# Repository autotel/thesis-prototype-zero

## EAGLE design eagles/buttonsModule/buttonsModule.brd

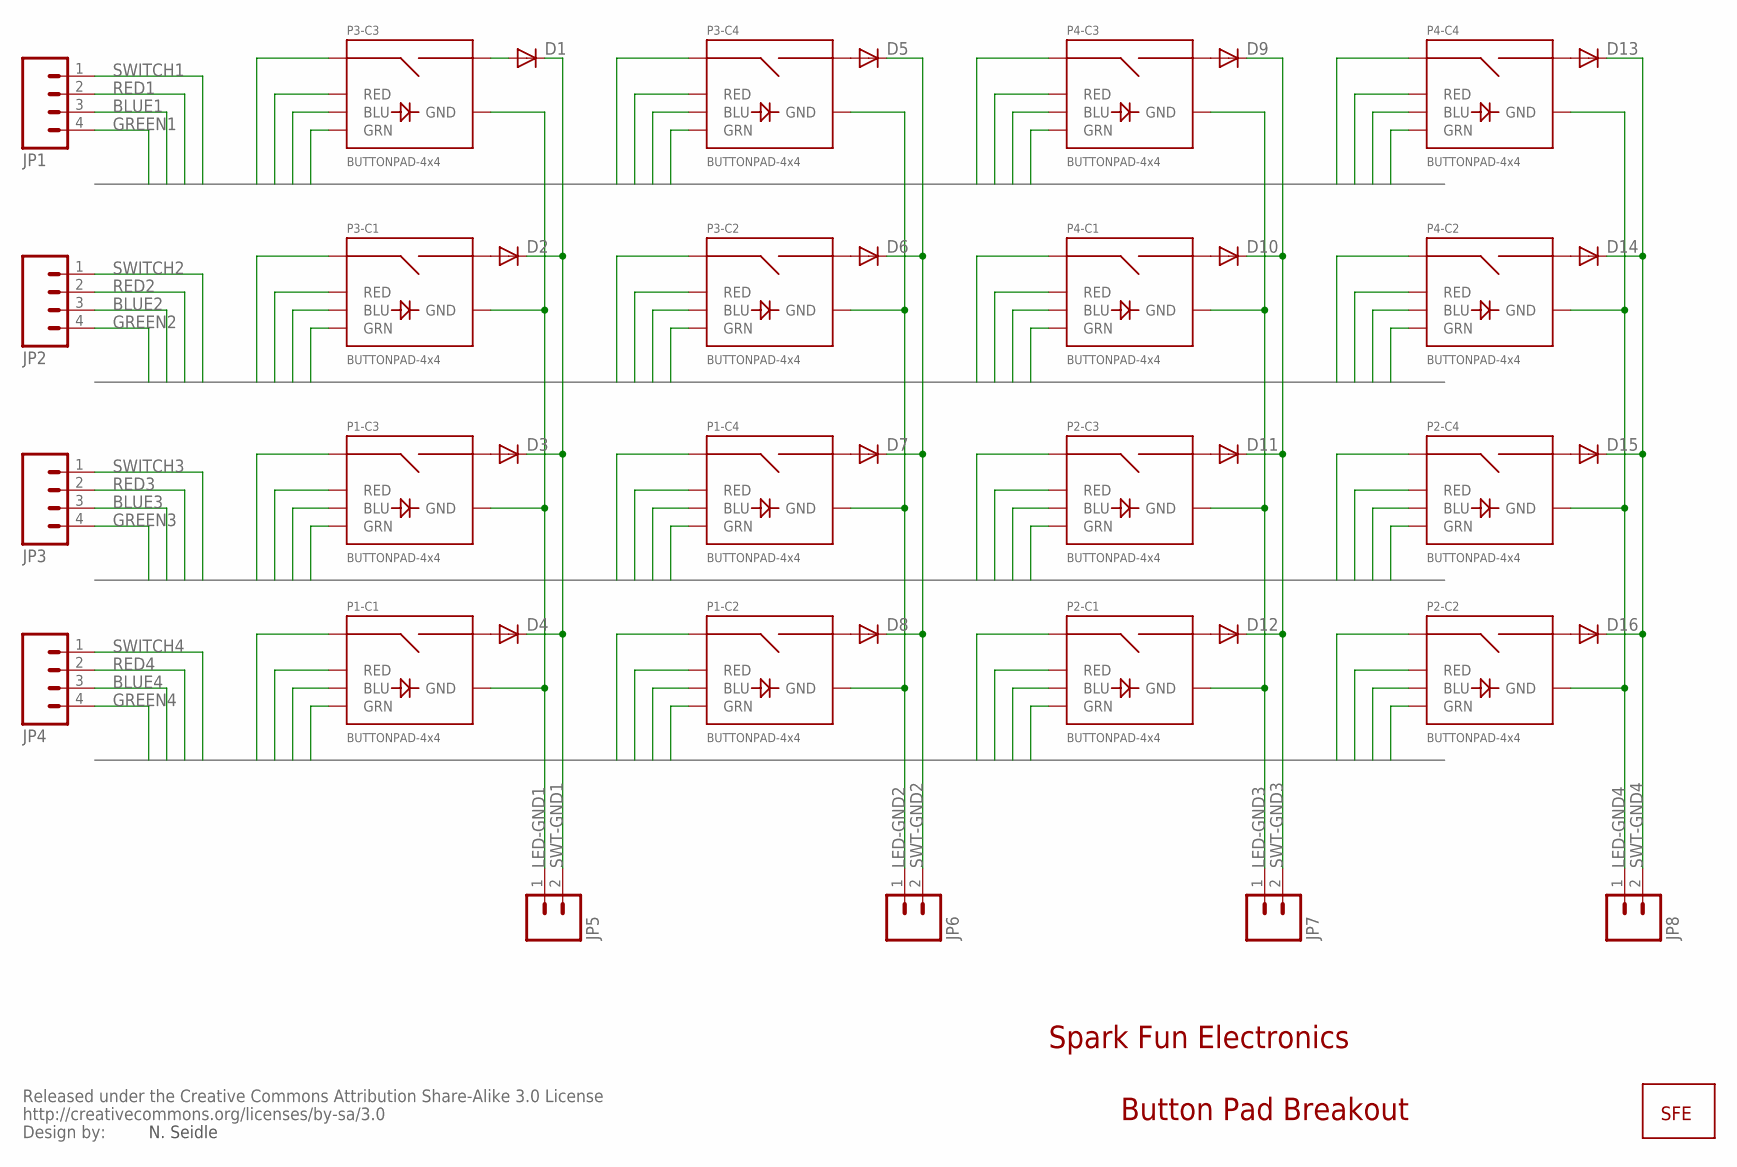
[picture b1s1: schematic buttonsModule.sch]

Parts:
D1, D2, D3, D4, D5, D6, D7, D8, D9, D10, D11, D12, D13, D14, D15, D16: DIODE-1N4148; DOIDE-1N4148
JP1, JP2, JP3, JP4: M04POLAR; MOLEX-1X4
JP5, JP6, JP7, JP8: M02POLAR; MOLEX-1X2
P1, P2, P3, P4: BUTTONPAD-4x4; BUTTONPAD-2X2
U$1: LOGO-SFE; SFE-NEW-WEBLOGO
U$2: CREATIVE_COMMONS

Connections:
BLUE1: JP1.3, P3.BLU3 (BLU), P3.BLU4 (BLU), P4.BLU3 (BLU), P4.BLU4 (BLU)
BLUE2: JP2.3, P3.BLU1 (BLU), P3.BLU2 (BLU), P4.BLU1 (BLU), P4.BLU2 (BLU)
BLUE3: JP3.3, P1.BLU3 (BLU), P1.BLU4 (BLU), P2.BLU3 (BLU), P2.BLU4 (BLU)
BLUE4: JP4.3, P1.BLU1 (BLU), P1.BLU2 (BLU), P2.BLU1 (BLU), P2.BLU2 (BLU)
GREEN1: JP1.4, P3.GRN3 (GRN), P3.GRN4 (GRN), P4.GRN3 (GRN), P4.GRN4 (GRN)
GREEN2: JP2.4, P3.GRN1 (GRN), P3.GRN2 (GRN), P4.GRN1 (GRN), P4.GRN2 (GRN)
GREEN3: JP3.4, P1.GRN3 (GRN), P1.GRN4 (GRN), P2.GRN3 (GRN), P2.GRN4 (GRN)
GREEN4: JP4.4, P1.GRN1 (GRN), P1.GRN2 (GRN), P2.GRN1 (GRN), P2.GRN2 (GRN)
LED-GND1: JP5.1, P1.GND1 (GND), P1.GND3 (GND), P3.GND1 (GND), P3.GND3 (GND)
LED-GND2: JP6.1, P1.GND2 (GND), P1.GND4 (GND), P3.GND2 (GND), P3.GND4 (GND)
LED-GND3: JP7.1, P2.GND1 (GND), P2.GND3 (GND), P4.GND1 (GND), P4.GND3 (GND)
LED-GND4: JP8.1, P2.GND2 (GND), P2.GND4 (GND), P4.GND2 (GND), P4.GND4 (GND)
unnamed: D1.P$1 (A), P3.SIG6 (SIG2)
unnamed: D2.P$1 (A), P3.SIG2
unnamed: D3.P$1 (A), P1.SIG6 (SIG2)
unnamed: D4.P$1 (A), P1.SIG2
unnamed: D5.P$1 (A), P3.SIG8 (SIG2)
unnamed: D6.P$1 (A), P3.SIG4 (SIG2)
unnamed: D7.P$1 (A), P1.SIG8 (SIG2)
unnamed: D8.P$1 (A), P1.SIG4 (SIG2)
unnamed: D9.P$1 (A), P4.SIG6 (SIG2)
unnamed: D10.P$1 (A), P4.SIG2
unnamed: D11.P$1 (A), P2.SIG6 (SIG2)
unnamed: D12.P$1 (A), P2.SIG2
unnamed: D13.P$1 (A), P4.SIG8 (SIG2)
unnamed: D14.P$1 (A), P4.SIG4 (SIG2)
unnamed: D15.P$1 (A), P2.SIG8 (SIG2)
unnamed: D16.P$1 (A), P2.SIG4 (SIG2)
RED1: JP1.2, P3.RED3 (RED), P3.RED4 (RED), P4.RED3 (RED), P4.RED4 (RED)
RED2: JP2.2, P3.RED1 (RED), P3.RED2 (RED), P4.RED1 (RED), P4.RED2 (RED)
RED3: JP3.2, P1.RED3 (RED), P1.RED4 (RED), P2.RED3 (RED), P2.RED4 (RED)
RED4: JP4.2, P1.RED1 (RED), P1.RED2 (RED), P2.RED1 (RED), P2.RED2 (RED)
SWITCH1: JP1.1, P3.SIG5 (SIG1), P3.SIG7 (SIG1), P4.SIG5 (SIG1), P4.SIG7 (SIG1)
SWITCH2: JP2.1, P3.SIG1, P3.SIG3 (SIG1), P4.SIG1, P4.SIG3 (SIG1)
SWITCH3: JP3.1, P1.SIG5 (SIG1), P1.SIG7 (SIG1), P2.SIG5 (SIG1), P2.SIG7 (SIG1)
SWITCH4: JP4.1, P1.SIG1, P1.SIG3 (SIG1), P2.SIG1, P2.SIG3 (SIG1)
SWT-GND1: D1.P$2 (C), D2.P$2 (C), D3.P$2 (C), D4.P$2 (C), JP5.2
SWT-GND2: D5.P$2 (C), D6.P$2 (C), D7.P$2 (C), D8.P$2 (C), JP6.2
SWT-GND3: D9.P$2 (C), D10.P$2 (C), D11.P$2 (C), D12.P$2 (C), JP7.2
SWT-GND4: D13.P$2 (C), D14.P$2 (C), D15.P$2 (C), D16.P$2 (C), JP8.2

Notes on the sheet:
Button Pad Breakout
Spark Fun Electronics
N. Seidle

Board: 2 copper layers, 30 parts (4 on the bottom side), 40 nets, no tracks yet.

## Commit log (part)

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2016-10-20 lcd working, encoder started
2016-10-26 hello button pads no multiplex (monochrome/row)
2016-10-27 leds now count one by one, completing the matrix program
2016-11-03 change led matrix pins to take them out from audio overlap
2016-11-03 idea for replacing lcd pins
2016-11-08 will not work
2016-11-08 mux is also problematic
2016-11-08 handy notes
2016-11-08 perfect led matrix applied to teensy
2016-11-09 undef var remove
2016-11-10 buttons not yet working but implemented
2016-11-14 buttons and led matrix working
2016-11-15 started pcb design
2016-11-16 first time i think that the schematic is ready
2016-11-16 FIX 16*4 pads error
2016-11-17 forward with the pcb design
2016-11-17 board PCB iteration prior to route
2016-11-17 fix big mistake on schematic
2016-11-17 first successful route
2016-11-18 routing job close
2016-11-18 expose contact terminals in button areas by applying solder mask
2016-11-19 successfully adapted the software for screen+button pad matrix using 16x muxes and arduino
2016-11-19 adapt portb connection to fit an LCD breakout
2016-11-19 routed last schematic change in the dip version
2016-11-22 tried to put ledmatrix libraries inside the libraries but couldn't because problems between static and instance modes that i don't understand
2016-11-28 starting to rollback intent to put all functionality in a library+ addition of barrel jack to pcb
2016-11-28 works, not 'libaried' anymore
2017-01-19 button toggle
2017-01-19 onButtonHeld
2017-01-22 midi style memory and interaction
2017-02-13 screeen slightly better, free up pins for screen
2017-02-13 lcd integrated in hardware
2017-02-14 more comments, activated intervace tact switches and duplicated to make a version with ui
2017-02-14 selector buttons now have onpress and onrelease funcs modeselector base
2017-02-14 modeselector is a modifier and not a mode
2017-02-14 cmplete ability to select channels, notes and playing modes using different user interaction schemes
2017-02-14 -split in multiple files - created the interaction for the scale design mode
2017-02-14 prototypes of cc modulation along with notes
2017-02-15 encoder activated notes for improvement of the PCB board
2017-02-16 body for the v2 prorotype started additional notes on the pcb design
2017-02-17 started creating the way for the sequencer, including changes in the ui and memory optimization fixed errors in the enclosure. There are still some to fix
2017-02-18 reduced use of dynamic memory by storing strings in PROGMEM
2017-02-18 basic and buggy implementation of sequencer mode with less memory usage
2017-02-28 checking different screen algorhythms to correct the problems
2017-02-28 changed some hardcoded vars with preprocessor vars
2017-03-02 fixed all known trouble with note matching in sequencer
2017-03-02 -fixed binding between matrix seleectors and the selected item (example: when selecting channel, buttons display last pressed button instead of actually selected channel, now they would represent the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
2017-03-02 - fix channel can't be selected scrolling, and modularized modes and POVS to avoid array index out of bounds when selecting higher ¨POV or MODE than available - put order in selector modes. there is 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
2017-03-03 many minor fixes
2017-03-03 started creating the function to find events in the perspective of ynamic modulus
2017-03-03 -rename pm_current with pov_current -more intuitive quantization when recording performance follows neares beat instead of currently running beat
2017-03-03 finished implementing the modulus based composition, but it takes a huge stake on processor time
2017-04-19 double microcontroller
2017-04-19 eliminate memory functions from display arduino
2017-05-09 testing using serial with node. the linbrary sucks bad
2017-05-10 figured out two way communication via serial (raspberry) and Fixed screen flickering!!
2017-05-10 stress testing the serial based physical interface showing good results
2017-05-11 can output midi using an usb midi interface
2017-05-11 files tidy up
2017-05-11 the firmware and the javascript script share the same constants
2017-05-11 trying to send strings didn't work
2017-05-12 set communicatiin trhough usb due to hardware problems, started testing interaction modes that are handled by the interface
2017-05-12 use arduino as screen for the raspberry maning that all data is handled in raspberry, and only grpahics data is sent to the arduino
2017-05-12 segregated interaction modes javascript node brain
2017-05-12 index on virtual-modular-uno-is-screen: 5c9fb7c hardware manager is part of environment so mode handlers can draw
2017-05-12 nice reduction of stuff in arduino, but still can't figure out why it doesnt work
2017-05-12 could write to the led matrix from the main index js but now the communication back is corrupted
2017-05-12 kind of working
2017-05-17 free the serial pins replacing them with two analog pins. generated problem with refresh rate
2017-05-17 fixed problem with refresh rate was due to making a softwareserial using the hardware serial pins, probably using inverted RX TX pin roles
2017-05-17 move the screen a bit up so it fits with the actual pcb
2017-05-17 same mapping for void readMuxB
2017-05-17 fix couple of errors in last commit
2017-05-17 prototype for reception of typed arrays of different lengths
2017-05-17 typed message with many lengths implemented using real constants
2017-05-17 node cuts and receives messages properly according to constants lengths
2017-05-17 fixed some issues with communication. still problems with transmision of pixels
2017-05-18 found solution to commmunication problem. it was because message didn't arrive complete yet when it was already out of the receiving loop. the message slicing should be done in the reception loop, an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
2017-05-18 implemented the same algorythm in the arduino side than in the node side, eliminating the requirement to delay() to receive the whole message. works like a charm
2017-05-18 mode engagement, and handling of metronome steps in modes there was a confilct where a mode that is not engaged will override the screen display of other modes if it had a listener that required scre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
2017-05-18 implemented a n-length data serial transmission
2017-05-19 sequencer dimension selector submode
2017-05-19 basic code cleaning in the firmware
2017-05-19 a bit healthier message sending, using a global array instead of local
2017-05-19 designing how the note is input in the sequencer
2017-05-19 implementing midi notes and interaction with scale setter
2017-05-22 implementing better filters will need to reestructure destinations
2017-05-22 many sequencers, finished implementing better filters and changing the interaction for layering
2017-05-22 fixed many severe errors that were curiously not causing problems. perhaps these were the origin of serial noise
2017-05-22 program encoder press detection which is not working anyways
2017-05-22 half way doing the preset kit creator
2017-05-23 a bit better interaction with system mode
2017-05-24 truncate screen messages to space available
2017-05-24 loop length and displace selector
2017-05-26 finished adding sequencer event filtering, started implementing note lengths
2017-05-26 implemented note lengths in sequencer, with some bugs
2017-05-26 loop look can be turned off
2017-05-26 created pat length folding, but still implementing the events duplicator
2017-05-28 less console logs, don't propagate null messages to event handler
2017-05-28 I apparently fixed the communication problem with the harware that was haunting.
2017-05-28 fixed that event emission from kit went off when I chaged dimension selector remove some console.logs
2017-06-01 change start command bacause with sound was too slow
2017-06-01 copy base of server taken from node-patternplatform; not integrated yet
2017-06-01 rename 'destinations' as 'modules' gives clearer idea of function behind
2017-06-01 reestructure server as optional subsidiary of environment changed how patcher modules are created in order to create event handlers more easily
2017-06-01 more general structure of the server
2017-06-02 framework that allows one server side module to be represented by several force directed nodes
2017-06-02 rename modes into modulex16 interfaces, will suggest how to add different hardware support in the future and is easier to understand
2017-06-02 reestructuration continues created an add module interaction mode, renamed some variables and files modules are singletons that can create instances dynamic elements naming changed more structures
2017-06-02 make singleton-instanced structures of the interaction modes similar to the one of the modules. rename interaction modes by type
2017-06-03 finally closed the loop of dynamically adding a module with it's interface
2017-06-03 further with the modular reestructuring
2017-06-03 loading default config from json didnt allow for more than one copy of each type of module. now it allows
2017-06-04 started to separate the sequencer between interface and function
2017-06-04 segregation of the sequencer: it runs, but not finsihed yet
2017-06-04 clear console.logs
2017-06-05 links data binding
2017-06-06 emission of eventMessages to clientside
2017-06-06 clocks were not emitting sub there was an error evaluating wether message had sub, because 0 evaluates false
2017-06-06 kit controller was not multi instanceable sequencer was not eventing the subs well
2017-06-06 preset kit was not propagating received messages,
2017-06-06 change forces a bit
2017-06-07 anti drifting 1
2017-06-07 loop folding would remove all the pattern if it was being shrunk rename controlledDestination into controlledModule in many modulecontrollers to give a clearer idea of the var
2017-06-07 sequencer loop displace
2017-06-07 fixed a bug where step events created by the folder were wrong
2017-06-07 loop folding was not propagaing to loop length actually
2017-06-08 muting presets presetkit
2017-06-08 better quantization for recorded sequencer events fixed yet another error in the muting of the presetkit
2017-06-08 note lengths were not being recorded
2017-06-08 sequencers have clock input by default, if there is a bus named "deft. clock bus" to make it easier
2017-06-09 sequencer that received a new recorded pat will switch to the destination that will show the new events
2017-06-09 add a special mark if the same module is chosen as output
2017-06-09 fixed mistake in previus commit
2017-06-09 the clock is now apparently perfect
2017-06-10 fixed modules muting and make noteoff on param change in presetkit
2017-06-10 fix mistake
2017-07-07 fixed problem of double triggering while recording, that was due to wrong event quantization
2017-07-07 make grade just work
2017-07-14 create chordkit interaction
2017-07-20 added raspberry anchoring holes and ventilation
2017-07-20 todos for 31st presentation
2017-07-20 half way implementing performance and recording in chordkit
2017-07-21 chordkit is working recording broke for some reason
2017-07-25 add "transparent" events, solve some errors in chordKit, eventMessage super and underimpose
2017-07-25 precarious implementation of basenote in the chordkit
2017-07-26 fix many errors with the chordkit
2017-07-27 after many tries, I resolved to implement a recording that chooses wether to record modules ui input or module's output, potentially allowing two features that were wanted
2017-07-27 two-folded recording from chordkit aswell
2017-07-27 display lengths of notes, also when creating a new note in a sequencer
2017-07-27 muting a sequencer would most likely generate hanging notes because the noteoff tracker was muted aswell
2017-07-27 show current selected preset presetkit
2017-09-29 cleanup of kicad folder
2017-09-29 cleanup kicad
2017-09-29 redesign of specs after experimenting and thinking
2017-09-29 improvement of last commit
2017-09-29 restart sequencer with a selector button combination+matrix button

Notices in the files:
parts and their libraries:
SparkFun: Released under the Creative Commons Attribution Share-Alike 3.0 License
SparkFun: http://creativecommons.org/licenses/by-sa/3.0
